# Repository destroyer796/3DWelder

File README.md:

# 3DWelder
This is an overbuilt 3D pen designed to be used for "welding" 3D printed parts together using 1.75mm filament. This project is funded by [Hack Club](https://hackclub.com/) as a part of the [Highway](https://highway.hackclub.com/) program.

Keep in mind for time being PCB is not working, I'll update soon.

This design uses a CHC Pro hotend and a custom Orbiter extruder adapted to use a DC motor. This DC motor's speed is controlled by a drill trigger adapted into the handle. It has a small screen and a rotary encoder for adjusting and showing the temperature target. The whole thing is powered by a drill battery to make it more portable and easier to use. This project is currently completely untested.

## Why?
So, why did I choose to make this ridiculous thing anyways? Well, the best way to join 3D printed parts together if they can't be screwed is by literally joining them together with the same plastic they're made of. This can be very difficult with a normal 3D pen though, as they're quite low powered and actually can't even melt many higher temperature plastics. I wanted a solution to this, so I decided to basically make a regular 3D printer extruding setup, but make it portable. It has some other uses aswell, if you use EVA filament, it could function essentially as a hot glue gun. It could also theoretically be used as a 3D pen, but not that well.

## PCB

The pcb was designed using KiCad, and it is only 2 layers. The pcb controlls everything except for voltage control and the motor, which is controlled by the drill trigger. It uses screw terminals and jst-xh connections. The brains of the whole thing is an Arduino Nano.

## Wiring/Assembly

All 3D printed parts screw together using M3 heatset inserts and various M3/M4 screws. For wiring, 2 spade connectors are used as terminals on the battery. From there, there's 2 ways of wiring everything else. You can either put the buck converter inside the space above the battery, then have wires coming off of that to the drill trigger and pcb, or have the buck converter up by the pcb, then have wires going back down to the drill trigger. Having the Buck converter in the handle is much cleaner, but may be very difficult to fit inside that small space.

## Code
<details>
  <summary>
    Arduino Code
  </summary>
  
  ~~~
  #include <PID_v1.h>
  #include <Adafruit_SSD1306.h>
  #include <Adafruit_GFX.h>
  #include <Wire.h>
  
  //Defines screen width/height
  #define SCREEN_WIDTH 128
  #define SCREEN_HEIGHT 32
  
  //Not using a reset pin
  #define OLED_RESET -1
  
  //Creates a display named display, gives it parameters
  Adafruit_SSD1306 display(SCREEN_WIDTH, SCREEN_HEIGHT, &Wire, OLED_RESET);
  
  // EC11 code
  const int EC11PinA = 8;
  const int EC11PinB = 7;
  volatile in encoderPos = 0;
  in lastEncoded = 0;
  
  /* -----------  USER SETTINGS  ----------- */
  const int   thermistorPin   = A0;
  const int   heaterPin       = 6;     // PWM pin
  const int   statusLedPin    = 13;    // Built‑in LED on most Arduinos
  const float R_FIXED         = 100000.0;   // 100 kΩ divider resistor
  
  // Steinhart–Hart coefficients for Semitec 104GT‑2 / 104NT
  const float A = 1.009249522e-3;
  const float B = 2.378405444e-4;
  const float C = 2.019202697e-7;
  
  // PID tuning
  double Kp = 4.0, Ki = 0.3, Kd = 12.0;
  
  /* Temperature targets */
  double setpointC   = 60.0;   // Desired temperature
  const double MAX_TEMP_C      = 300.0;   // Hard safety limit
  const double MIN_VALID_VOLT  = 0.10;   // Thermistor‑open detection
  
  /* -----------  GLOBALS  ----------- */
  double inputC, outputPWM;          // For PID library
  PID myPID(&inputC, &outputPWM, &setpointC, Kp, Ki, Kd, DIRECT);
  
  enum FaultState { OK, OVER_TEMPERATURE, SENSOR_ERROR };
  FaultState fault = OK;
  
  /* Timing helpers */
  unsigned long lastBlink   = 0;
  bool          ledState    = false;
  
  void setup() {
    //Start I2C
    Wire.begin();
  
    // Initializes display using I2C address 0x3C, if it fails it prints error message
    // Switchcapvcc thing tells it that display has internal voltage regulator
    if (!display.begin(SSD1306_SWITCHCAPVCC, 0x3C)) {
      Serial.begin(9600);
      Serial.println(F("SSD1306 allocation failed"));
      for (;;);
    }
  
    //Display test commands
    display.clearDisplay(); // Clears display
    display.setTextSize(1); // Sets text size, 1 = 6/8 pixels, 5/7 without spacing, 2 = 2x, 3 = 3x
    display.setTextColor(SSD1306_WHITE); // Set white text
    display.setCursor(0,0); // Sets cursor to top-left
    display.println(F("Hello SH-S091!")); // Print message to display buffer
    display.display(); // Push everything in buffer to scren
    // display.setFont(), allows you to change fonts, need to install them
    // display.fillRect(x, y, width, height, SSD1306_BLACK) draws a black rect, way to clear part of screen
  
    //EC11 Code
    pinMode(EC11PinA, INPUT_PULLUP);
    pinMode(EC11PinB, INPUT_PULLUP);
    attachInterrupt(digitalPinToInterrupt(EC11PinA), updateEncoder, CHANGE);
    attachInterrupt(digitalPinToInterrupt(EC11PinB), updateEncoder, CHANGE);

    pinMode(heaterPin,   OUTPUT);
    pinMode(statusLedPin, OUTPUT);
    Serial.begin(9600);
  
    myPID.SetOutputLimits(0, 255);
    myPID.SetSampleTime(250);          // 4 Hz PID updates
    myPID.SetMode(AUTOMATIC);
  }
  
  void loop() {
    //EC11 Code
    static int lastPos = 0;
    if (encoderPos != lastPos) {
      Serial.print("Value: ");
      Serial.println(encoderPos);
  
      display.fillRect(0, 0, 64, 32, SSD1306_BLACK);
      display.setTextSize(1);
      display.setTextColor(SSD1306_WHITE);
      display.setCursor(0,0);
      display.println(F(encoderPos));
      display.display
  
      lastPos = encoderPos;
    }

    /* ---------- Read thermistor ---------- */
    int   adc = analogRead(thermistorPin);
    float v   = adc * 5.0 / 1023.0;
  
    /* Sensor fault check */
    if (v < MIN_VALID_VOLT)  fault = SENSOR_ERROR;
  
    /* Convert to °C if no sensor fault */
    if (fault == OK) {
      double R = R_FIXED * (5.0 / v - 1.0);
      double lnR = log(R);
      double tempK = 1.0 / (A + B*lnR + C*lnR*lnR*lnR);
      inputC = tempK - 273.15;
  
      /* Over‑temperature check */
      if (inputC >= MAX_TEMP_C) fault = OVER_TEMPERATURE;
    }
  
    /* ---------- Safety Handling ---------- */
    if (fault != OK) {
      myPID.SetMode(MANUAL);       // Freeze PID
      outputPWM = 0;               // Heater OFF
      analogWrite(heaterPin, 0);
    } else {
      myPID.Compute();             // Let PID calculate outputPWM
      analogWrite(heaterPin, (int)outputPWM);
    }
  
    /* ---------- Status LED ----------
       • ON  …… actively heating (PWM > 0)
       • Slow blink …… at set‑point (PID output ~0)
       • Fast blink …… fault
    ---------------------------------- */
    unsigned long now = millis();
    unsigned long blinkPeriod =
        (fault != OK)          ? 150 :        // fast blink on fault
        (outputPWM < 2)        ? 800 :        // slow blink at set‑point
                                 0;           // solid ON while heating
  
    if (blinkPeriod == 0) {
      digitalWrite(statusLedPin, HIGH);
    } else if (now - lastBlink >= blinkPeriod) {
      ledState = !ledState;
      digitalWrite(statusLedPin, ledState);
      lastBlink = now;
    }
  
    /* ---------- Serial Monitor ---------- */
    Serial.print("Temp: ");
    Serial.print((fault == OK) ? inputC : NAN);
    Serial.print(" °C | PWM: ");
    Serial.print(outputPWM);
    Serial.print(" | Fault: ");
    Serial.println(
        (fault == OK) ? "None" :
        (fault == OVER_TEMPERATURE) ? "Over-Temp" : "Sensor Error");

    // Shows temp on display
    display.fillRect(64, 0, 64, 32, SSD1306_BLACK);
    display.setTextSize(1);
    display.setTextColor(SSD1306_WHITE);
    display.setCursor(64,0);
    display.println(F(inputC));
    display.display
  }
  
  //EC11 code, runs everytime a change in position is detected
  void updateEncoder() {
    int MSB = digitalREad(EC11PinA);
    int LSB = digitalRead(EC11PinB);
  
    int encoded = (MSB << 1) | LSB;
    int sum = (lastEncocded << 2) | encoded;
  
    //Clockwise
    if (sum == 0b1101 || sum == 0b0100 || sum == 0b0010 || sum == 0b1011) {
      encoderPos += 5;
    }
    //Counter-Clockwise
    if (sum == 0b1110 || sum == 0b0111 || sum == 0b0001 || sum == 0b1000) {
      encoderPos -= 5;
    }
  
    lastEncoded = encoded
  }
  ~~~

</details>

This is the firmware to be uploaded to the Arduino Nano. It's purpose is for PID control of the heater via the thermistor readings and mosfet. It has temperature control via the EC11 rotary encoder, and the temperature target and current temperature are displayed on the 0.91 inch OLED screen.

## BOM

| Item | Quantity | Price | Source | Notes | Owned/Buying |
|--------|--------|--------|--------|--------|--------|
| Drill Trigger | 1 | $3.57 | [Aliexpress](https://www.aliexpress.com/item/3256806562336203.html?spm=a2g0o.cart.0.0.755738danhf7AI&mp=1&pdp_npi=5%40dis%21USD%21USD%209.39%21USD%203.57%21%21USD%203.57%21%21%21%402103146c17528271550647744ef8ea%2112000038176249576%21ct%21US%212965353747%21%211%210&_gl=1*1qs30jx*_gcl_aw*R0NMLjE3NTE4NDcxMzYuQ2owS0NRand2YWpEQmhDTkFSSXNBRUUyOVdvb1JYN0FnSzczYmNCVXN5VHRNRGlUUjV4QXJ0RzRDSVl6Tmx5ZEZ2alByYWdRQjczVklkSWFBc3FnRUFMd193Y0I.*_gcl_dc*R0NMLjE3NTE4NDcxMzYuQ2owS0NRand2YWpEQmhDTkFSSXNBRUUyOVdvb1JYN0FnSzczYmNCVXN5VHRNRGlUUjV4QXJ0RzRDSVl6Tmx5ZEZ2alByYWdRQjczVklkSWFBc3FnRUFMd193Y0I.*_gcl_au*MTM0OTQyNjgzMy4xNzUwMTkyNzY4*_ga*MjcyMzA3OTUzLjE3NTI4MjM0NjE.*_ga_VED1YSGNC7*czE3NTI4MjM0NjEkbzEkZzEkdDE3NTI4MjcwNjAkajU5JGwwJGgw) | For regulating motor | Buying |
| CHC Pro | 1 | $22.42 | [Aliexpress](https://www.aliexpress.com/item/3256806914810913.html?spm=a2g0o.cart.0.0.755738daw2eCeF&mp=1&pdp_npi=5%40dis%21USD%21USD%2049.83%21USD%2022.42%21%21USD%2022.42%21%21%21%402101e07217528229181472693e61f9%2112000045551090949%21ct%21US%212965353747%21%211%210&_gl=1*1s341fi*_gcl_aw*R0NMLjE3NTE4NDcxMzYuQ2owS0NRand2YWpEQmhDTkFSSXNBRUUyOVdvb1JYN0FnSzczYmNCVXN5VHRNRGlUUjV4QXJ0RzRDSVl6Tmx5ZEZ2alByYWdRQjczVklkSWFBc3FnRUFMd193Y0I.*_gcl_dc*R0NMLjE3NTE4NDcxMzYuQ2owS0NRand2YWpEQmhDTkFSSXNBRUUyOVdvb1JYN0FnSzczYmNCVXN5VHRNRGlUUjV4QXJ0RzRDSVl6Tmx5ZEZ2alByYWdRQjczVklkSWFBc3FnRUFMd193Y0I.*_gcl_au*MTM0OTQyNjgzMy4xNzUwMTkyNzY4*_ga*MjcyMzA3OTUzLjE3NTI4MjM0NjE.*_ga_VED1YSGNC7*czE3NTI4MjM0NjEkbzEkZzEkdDE3NTI4MjM1OTkkajIwJGwwJGgw) | Hotend | Buying |
| Screw Terminal 4P | 1 | $2.50 | [Aliexpress](https://www.aliexpress.com/item/3256807282935438.html?spm=a2g0o.cart.0.0.755738danhf7AI&mp=1&pdp_npi=5%40dis%21USD%21USD%202.59%21USD%202.50%21%21USD%202.50%21%21%21%402103146c17528271550647744ef8ea%2112000040883353771%21ct%21US%212965353747%21%211%210&_gl=1*1qs30jx*_gcl_aw*R0NMLjE3NTE4NDcxMzYuQ2owS0NRand2YWpEQmhDTkFSSXNBRUUyOVdvb1JYN0FnSzczYmNCVXN5VHRNRGlUUjV4QXJ0RzRDSVl6Tmx5ZEZ2alByYWdRQjczVklkSWFBc3FnRUFMd193Y0I.*_gcl_dc*R0NMLjE3NTE4NDcxMzYuQ2owS0NRand2YWpEQmhDTkFSSXNBRUUyOVdvb1JYN0FnSzczYmNCVXN5VHRNRGlUUjV4QXJ0RzRDSVl6Tmx5ZEZ2alByYWdRQjczVklkSWFBc3FnRUFMd193Y0I.*_gcl_au*MTM0OTQyNjgzMy4xNzUwMTkyNzY4*_ga*MjcyMzA3OTUzLjE3NTI4MjM0NjE.*_ga_VED1YSGNC7*czE3NTI4MjM0NjEkbzEkZzEkdDE3NTI4MjcwNjAkajU5JGwwJGgw) | 7.62mm pitch, Power inputs | Buying |
| Screw Terminal 2P | 1 | $1.87 | [Aliexpress](https://www.aliexpress.com/item/3256807282935438.html?spm=a2g0o.cart.0.0.755738danhf7AI&mp=1&pdp_npi=5%40dis%21USD%21USD%201.94%21USD%201.87%21%21USD%201.87%21%21%21%402103146c17528271550647744ef8ea%2112000040883353769%21ct%21US%212965353747%21%211%210&_gl=1*1qs30jx*_gcl_aw*R0NMLjE3NTE4NDcxMzYuQ2owS0NRand2YWpEQmhDTkFSSXNBRUUyOVdvb1JYN0FnSzczYmNCVXN5VHRNRGlUUjV4QXJ0RzRDSVl6Tmx5ZEZ2alByYWdRQjczVklkSWFBc3FnRUFMd193Y0I.*_gcl_dc*R0NMLjE3NTE4NDcxMzYuQ2owS0NRand2YWpEQmhDTkFSSXNBRUUyOVdvb1JYN0FnSzczYmNCVXN5VHRNRGlUUjV4QXJ0RzRDSVl6Tmx5ZEZ2alByYWdRQjczVklkSWFBc3FnRUFMd193Y0I.*_gcl_au*MTM0OTQyNjgzMy4xNzUwMTkyNzY4*_ga*MjcyMzA3OTUzLjE3NTI4MjM0NjE.*_ga_VED1YSGNC7*czE3NTI4MjM0NjEkbzEkZzEkdDE3NTI4MjcwNjAkajU5JGwwJGgw) | 7.62mm pitch, Heater outputs | Buying |
| 2510 24V Fan | 1 | $2.08 | [Aliexpress](https://www.aliexpress.com/item/3256807251337149.html?spm=a2g0o.cart.0.0.755738danhf7AI&mp=1&pdp_npi=5%40dis%21USD%21USD%202.18%21USD%202.08%21%21USD%202.08%21%21%21%402103146c17528271550647744ef8ea%2112000040754390185%21ct%21US%212965353747%21%211%210&_gl=1*1qs30jx*_gcl_aw*R0NMLjE3NTE4NDcxMzYuQ2owS0NRand2YWpEQmhDTkFSSXNBRUUyOVdvb1JYN0FnSzczYmNCVXN5VHRNRGlUUjV4QXJ0RzRDSVl6Tmx5ZEZ2alByYWdRQjczVklkSWFBc3FnRUFMd193Y0I.*_gcl_dc*R0NMLjE3NTE4NDcxMzYuQ2owS0NRand2YWpEQmhDTkFSSXNBRUUyOVdvb1JYN0FnSzczYmNCVXN5VHRNRGlUUjV4QXJ0RzRDSVl6Tmx5ZEZ2alByYWdRQjczVklkSWFBc3FnRUFMd193Y0I.*_gcl_au*MTM0OTQyNjgzMy4xNzUwMTkyNzY4*_ga*MjcyMzA3OTUzLjE3NTI4MjM0NjE.*_ga_VED1YSGNC7*czE3NTI4MjM0NjEkbzEkZzEkdDE3NTI4MjcwNjAkajU5JGwwJGgw) | Cools hotend | Owned |
| EC11 Rotary Encoder | 1 | $3.08 | [Aliexpress](https://www.aliexpress.com/item/3256805796819763.html?spm=a2g0o.cart.0.0.755738danhf7AI&mp=1&pdp_npi=5%40dis%21USD%21USD%203.08%21USD%203.08%21%21USD%203.08%21%21%21%402103146c17528271550647744ef8ea%2112000035172713579%21ct%21US%212965353747%21%211%210&_gl=1*1gfgklc*_gcl_aw*R0NMLjE3NTE4NDcxMzYuQ2owS0NRand2YWpEQmhDTkFSSXNBRUUyOVdvb1JYN0FnSzczYmNCVXN5VHRNRGlUUjV4QXJ0RzRDSVl6Tmx5ZEZ2alByYWdRQjczVklkSWFBc3FnRUFMd193Y0I.*_gcl_dc*R0NMLjE3NTE4NDcxMzYuQ2owS0NRand2YWpEQmhDTkFSSXNBRUUyOVdvb1JYN0FnSzczYmNCVXN5VHRNRGlUUjV4QXJ0RzRDSVl6Tmx5ZEZ2alByYWdRQjczVklkSWFBc3FnRUFMd193Y0I.*_gcl_au*MTM0OTQyNjgzMy4xNzUwMTkyNzY4*_ga*MjcyMzA3OTUzLjE3NTI4MjM0NjE.*_ga_VED1YSGNC7*czE3NTI4MjM0NjEkbzEkZzEkdDE3NTI4MjcwNjAkajU5JGwwJGgw) | For controlling temp | Buying |
| I2C OLED | 1 | $1.85 | [Aliexpress](https://www.aliexpress.com/item/3256806179530924.html?spm=a2g0o.cart.0.0.755738danhf7AI&mp=1&pdp_npi=5%40dis%21USD%21USD%204.03%21USD%201.85%21%21USD%201.85%21%21%21%402103146c17528271550647744ef8ea%2112000036911966887%21ct%21US%212965353747%21%211%210&_gl=1*1gfgklc*_gcl_aw*R0NMLjE3NTE4NDcxMzYuQ2owS0NRand2YWpEQmhDTkFSSXNBRUUyOVdvb1JYN0FnSzczYmNCVXN5VHRNRGlUUjV4QXJ0RzRDSVl6Tmx5ZEZ2alByYWdRQjczVklkSWFBc3FnRUFMd193Y0I.*_gcl_dc*R0NMLjE3NTE4NDcxMzYuQ2owS0NRand2YWpEQmhDTkFSSXNBRUUyOVdvb1JYN0FnSzczYmNCVXN5VHRNRGlUUjV4QXJ0RzRDSVl6Tmx5ZEZ2alByYWdRQjczVklkSWFBc3FnRUFMd193Y0I.*_gcl_au*MTM0OTQyNjgzMy4xNzUwMTkyNzY4*_ga*MjcyMzA3OTUzLjE3NTI4MjM0NjE.*_ga_VED1YSGNC7*czE3NTI4MjM0NjEkbzEkZzEkdDE3NTI4MjcwNjAkajU5JGwwJGgw) | 0.91in, Displays target/current temp | Buying |
| TO-220 Radiator | 1 | $1.94 | [Aliexpress](https://www.aliexpress.com/item/2255800003999447.html?spm=a2g0o.cart.0.0.755738danhf7AI&mp=1&pdp_npi=5%40dis%21USD%21USD%202.01%21USD%201.94%21%21USD%201.94%21%21%21%402103146c17528271550647744ef8ea%2110000000710306628%21ct%21US%212965353747%21%211%210&_gl=1*1gfgklc*_gcl_aw*R0NMLjE3NTE4NDcxMzYuQ2owS0NRand2YWpEQmhDTkFSSXNBRUUyOVdvb1JYN0FnSzczYmNCVXN5VHRNRGlUUjV4QXJ0RzRDSVl6Tmx5ZEZ2alByYWdRQjczVklkSWFBc3FnRUFMd193Y0I.*_gcl_dc*R0NMLjE3NTE4NDcxMzYuQ2owS0NRand2YWpEQmhDTkFSSXNBRUUyOVdvb1JYN0FnSzczYmNCVXN5VHRNRGlUUjV4QXJ0RzRDSVl6Tmx5ZEZ2alByYWdRQjczVklkSWFBc3FnRUFMd193Y0I.*_gcl_au*MTM0OTQyNjgzMy4xNzUwMTkyNzY4*_ga*MjcyMzA3OTUzLjE3NTI4MjM0NjE.*_ga_VED1YSGNC7*czE3NTI4MjM0NjEkbzEkZzEkdDE3NTI4MjcwNjAkajU5JGwwJGgw) | Cools mosfet | Buying |
| IRLZ34NPBF Mosfet | 1 | $3.20 | [Aliexpress](https://www.aliexpress.com/item/3256808552158121.html?spm=a2g0o.cart.0.0.755738danhf7AI&mp=1&pdp_npi=5%40dis%21USD%21USD%206.97%21USD%203.20%21%21USD%203.20%21%21%21%402103146c17528271550647744ef8ea%2112000046468959878%21ct%21US%212965353747%21%211%210&_gl=1*1gfgklc*_gcl_aw*R0NMLjE3NTE4NDcxMzYuQ2owS0NRand2YWpEQmhDTkFSSXNBRUUyOVdvb1JYN0FnSzczYmNCVXN5VHRNRGlUUjV4QXJ0RzRDSVl6Tmx5ZEZ2alByYWdRQjczVklkSWFBc3FnRUFMd193Y0I.*_gcl_dc*R0NMLjE3NTE4NDcxMzYuQ2owS0NRand2YWpEQmhDTkFSSXNBRUUyOVdvb1JYN0FnSzczYmNCVXN5VHRNRGlUUjV4QXJ0RzRDSVl6Tmx5ZEZ2alByYWdRQjczVklkSWFBc3FnRUFMd193Y0I.*_gcl_au*MTM0OTQyNjgzMy4xNzUwMTkyNzY4*_ga*MjcyMzA3OTUzLjE3NTI4MjM0NjE.*_ga_VED1YSGNC7*czE3NTI4MjM0NjEkbzEkZzEkdDE3NTI4MjcwNjAkajU5JGwwJGgw) | TO-220, Regulates hotend heater | Buying |
| 24V-12V Buck Converter | 1 | $4.12 | [Aliexpress](https://www.aliexpress.com/item/3256805319593185.html?spm=a2g0o.cart.0.0.755738danhf7AI&mp=1&pdp_npi=5%40dis%21USD%21USD%204.12%21USD%204.12%21%21USD%204.12%21%21%21%402103146c17528271550647744ef8ea%2112000033343621926%21ct%21US%212965353747%21%211%210&_gl=1*1gfgklc*_gcl_aw*R0NMLjE3NTE4NDcxMzYuQ2owS0NRand2YWpEQmhDTkFSSXNBRUUyOVdvb1JYN0FnSzczYmNCVXN5VHRNRGlUUjV4QXJ0RzRDSVl6Tmx5ZEZ2alByYWdRQjczVklkSWFBc3FnRUFMd193Y0I.*_gcl_dc*R0NMLjE3NTE4NDcxMzYuQ2owS0NRand2YWpEQmhDTkFSSXNBRUUyOVdvb1JYN0FnSzczYmNCVXN5VHRNRGlUUjV4QXJ0RzRDSVl6Tmx5ZEZ2alByYWdRQjczVklkSWFBc3FnRUFMd193Y0I.*_gcl_au*MTM0OTQyNjgzMy4xNzUwMTkyNzY4*_ga*MjcyMzA3OTUzLjE3NTI4MjM0NjE.*_ga_VED1YSGNC7*czE3NTI4MjM0NjEkbzEkZzEkdDE3NTI4MjcwNjAkajU5JGwwJGgw) | Converts battery 24V to 12V for Arduino | Buying |
| DC Motor | 1 | $13.35 | [Aliexpress](https://www.aliexpress.com/item/3256807142640791.html?spm=a2g0o.cart.0.0.755738danhf7AI&mp=1&pdp_npi=5%40dis%21USD%21USD%2029.02%21USD%2013.35%21%21USD%2013.35%21%21%21%402103146c17528271595267798ef8ea%2112000040287640067%21ct%21US%212965353747%21%211%210&_gl=1*1djn14*_gcl_aw*R0NMLjE3NTE4NDcxMzYuQ2owS0NRand2YWpEQmhDTkFSSXNBRUUyOVdvb1JYN0FnSzczYmNCVXN5VHRNRGlUUjV4QXJ0RzRDSVl6Tmx5ZEZ2alByYWdRQjczVklkSWFBc3FnRUFMd193Y0I.*_gcl_dc*R0NMLjE3NTE4NDcxMzYuQ2owS0NRand2YWpEQmhDTkFSSXNBRUUyOVdvb1JYN0FnSzczYmNCVXN5VHRNRGlUUjV4QXJ0RzRDSVl6Tmx5ZEZ2alByYWdRQjczVklkSWFBc3FnRUFMd193Y0I.*_gcl_au*MTM0OTQyNjgzMy4xNzUwMTkyNzY4*_ga*MjcyMzA3OTUzLjE3NTI4MjM0NjE.*_ga_VED1YSGNC7*czE3NTI4MjM0NjEkbzEkZzEkdDE3NTI4MjcwNjAkajU5JGwwJGgw) | 24V, Worm gear, 27rpm, drives extruder | Buying |
| Kobalt 24V Battery | 1 | $28.35 | [Aliexpress](https://www.aliexpress.com/item/3256808341351094.html?spm=a2g0o.cart.0.0.755738danhf7AI&mp=1&pdp_npi=5%40dis%21USD%21USD%2098.74%21USD%2028.35%21%21USD%2028.35%21%21%21%402103146c17528271595267798ef8ea%2112000045570945299%21ct%21US%212965353747%21%211%210&_gl=1*1djn14*_gcl_aw*R0NMLjE3NTE4NDcxMzYuQ2owS0NRand2YWpEQmhDTkFSSXNBRUUyOVdvb1JYN0FnSzczYmNCVXN5VHRNRGlUUjV4QXJ0RzRDSVl6Tmx5ZEZ2alByYWdRQjczVklkSWFBc3FnRUFMd193Y0I.*_gcl_dc*R0NMLjE3NTE4NDcxMzYuQ2owS0NRand2YWpEQmhDTkFSSXNBRUUyOVdvb1JYN0FnSzczYmNCVXN5VHRNRGlUUjV4QXJ0RzRDSVl6Tmx5ZEZ2alByYWdRQjczVklkSWFBc3FnRUFMd193Y0I.*_gcl_au*MTM0OTQyNjgzMy4xNzUwMTkyNzY4*_ga*MjcyMzA3OTUzLjE3NTI4MjM0NjE.*_ga_VED1YSGNC7*czE3NTI4MjM0NjEkbzEkZzEkdDE3NTI4MjcwNjAkajU5JGwwJGgw) | Any Ah, mines 6.0Ah, Powers whole thing | Buying |
| 100k Resistor | 1 | $1.27 | [Aliexpress](https://www.aliexpress.us/item/3256805491339263.html?spm=a2g0o.productlist.main.2.5acb113dWCWHEi&algo_pvid=d885d319-e63c-46cb-9890-1f3fe4b1ec6b&algo_exp_id=d885d319-e63c-46cb-9890-1f3fe4b1ec6b-1&pdp_ext_f=%7B%22order%22%3A%221339%22%2C%22eval%22%3A%221%22%7D&pdp_npi=4%40dis%21USD%211.88%211.26%21%21%2113.46%219.02%21%402103247917528275691891949e5c61%2112000033982954181%21sea%21US%212965353747%21X&curPageLogUid=0ChrWbtCVhkG&utparam-url=scene%3Asearch%7Cquery_from%3A) | For thermistor logic | Owned |
| 10k Resistor | 1 | $1.34 | [Aliexpress](https://www.aliexpress.us/item/3256805491339263.html?spm=a2g0o.productlist.main.2.5acb113dWCWHEi&algo_pvid=d885d319-e63c-46cb-9890-1f3fe4b1ec6b&algo_exp_id=d885d319-e63c-46cb-9890-1f3fe4b1ec6b-1&pdp_ext_f=%7B%22order%22%3A%221339%22%2C%22eval%22%3A%221%22%7D&pdp_npi=4%40dis%21USD%211.88%211.26%21%21%2113.46%219.02%21%402103247917528275691891949e5c61%2112000033982954181%21sea%21US%212965353747%21X&curPageLogUid=0ChrWbtCVhkG&utparam-url=scene%3Asearch%7Cquery_from%3A) | Heater gate pulldown | Owned |
| 220R Resistor | 1 | $1.35 | [Aliexpress](https://www.aliexpress.us/item/3256805491339263.html?spm=a2g0o.productlist.main.2.5acb113dWCWHEi&algo_pvid=d885d319-e63c-46cb-9890-1f3fe4b1ec6b&algo_exp_id=d885d319-e63c-46cb-9890-1f3fe4b1ec6b-1&pdp_ext_f=%7B%22order%22%3A%221339%22%2C%22eval%22%3A%221%22%7D&pdp_npi=4%40dis%21USD%211.88%211.26%21%21%2113.46%219.02%21%402103247917528275691891949e5c61%2112000033982954181%21sea%21US%212965353747%21X&curPageLogUid=0ChrWbtCVhkG&utparam-url=scene%3Asearch%7Cquery_from%3A) | Heater gate drive | Owned |
| 2 Pin JST XH Female | 2 | $2.37 | [Aliexpress](https://www.aliexpress.com/item/3256803235887618.html?spm=a2g0o.cart.0.0.755738danhf7AI&mp=1&pdp_npi=5%40dis%21USD%21USD%202.49%21USD%202.37%21%21USD%202.37%21%21%21%402103146c17528270600956401ef8ea%2112000025716082487%21ct%21US%212965353747%21%211%210&_gl=1*1djn14*_gcl_aw*R0NMLjE3NTE4NDcxMzYuQ2owS0NRand2YWpEQmhDTkFSSXNBRUUyOVdvb1JYN0FnSzczYmNCVXN5VHRNRGlUUjV4QXJ0RzRDSVl6Tmx5ZEZ2alByYWdRQjczVklkSWFBc3FnRUFMd193Y0I.*_gcl_dc*R0NMLjE3NTE4NDcxMzYuQ2owS0NRand2YWpEQmhDTkFSSXNBRUUyOVdvb1JYN0FnSzczYmNCVXN5VHRNRGlUUjV4QXJ0RzRDSVl6Tmx5ZEZ2alByYWdRQjczVklkSWFBc3FnRUFMd193Y0I.*_gcl_au*MTM0OTQyNjgzMy4xNzUwMTkyNzY4*_ga*MjcyMzA3OTUzLjE3NTI4MjM0NjE.*_ga_VED1YSGNC7*czE3NTI4MjM0NjEkbzEkZzEkdDE3NTI4MjcwNjAkajU5JGwwJGgw) | For fan and thermistor | Owned |
| 18 AWG Wire | ~2 meters | $2.11 | [Aliexpress](https://www.aliexpress.com/item/3256806379805687.html?spm=a2g0o.cart.0.0.755738danhf7AI&mp=1&pdp_npi=5%40dis%21USD%21USD%202.20%21USD%202.11%21%21USD%202.11%21%21%21%402103146c17528270600956401ef8ea%2112000037691464120%21ct%21US%212965353747%21%211%210&_gl=1*1djn14*_gcl_aw*R0NMLjE3NTE4NDcxMzYuQ2owS0NRand2YWpEQmhDTkFSSXNBRUUyOVdvb1JYN0FnSzczYmNCVXN5VHRNRGlUUjV4QXJ0RzRDSVl6Tmx5ZEZ2alByYWdRQjczVklkSWFBc3FnRUFMd193Y0I.*_gcl_dc*R0NMLjE3NTE4NDcxMzYuQ2owS0NRand2YWpEQmhDTkFSSXNBRUUyOVdvb1JYN0FnSzczYmNCVXN5VHRNRGlUUjV4QXJ0RzRDSVl6Tmx5ZEZ2alByYWdRQjczVklkSWFBc3FnRUFMd193Y0I.*_gcl_au*MTM0OTQyNjgzMy4xNzUwMTkyNzY4*_ga*MjcyMzA3OTUzLjE3NTI4MjM0NjE.*_ga_VED1YSGNC7*czE3NTI4MjM0NjEkbzEkZzEkdDE3NTI4MjcwNjAkajU5JGwwJGgw) | Wiring everything | Owned |
| Arduino Nano | 1 | $2.94 | [Aliexpress](https://www.aliexpress.com/item/3256806587205161.html?spm=a2g0o.cart.0.0.755738danhf7AI&mp=1&pdp_npi=5%40dis%21USD%21USD%202.94%21USD%202.94%21%21USD%202.94%21%21%21%402103146c17528270600956401ef8ea%2112000038256018925%21ct%21US%212965353747%21%211%210&_gl=1*6iw3e9*_gcl_aw*R0NMLjE3NTE4NDcxMzYuQ2owS0NRand2YWpEQmhDTkFSSXNBRUUyOVdvb1JYN0FnSzczYmNCVXN5VHRNRGlUUjV4QXJ0RzRDSVl6Tmx5ZEZ2alByYWdRQjczVklkSWFBc3FnRUFMd193Y0I.*_gcl_dc*R0NMLjE3NTE4NDcxMzYuQ2owS0NRand2YWpEQmhDTkFSSXNBRUUyOVdvb1JYN0FnSzczYmNCVXN5VHRNRGlUUjV4QXJ0RzRDSVl6Tmx5ZEZ2alByYWdRQjczVklkSWFBc3FnRUFMd193Y0I.*_gcl_au*MTM0OTQyNjgzMy4xNzUwMTkyNzY4*_ga*MjcyMzA3OTUzLjE3NTI4MjM0NjE.*_ga_VED1YSGNC7*czE3NTI4MjM0NjEkbzEkZzEkdDE3NTI4MjcwNjAkajU5JGwwJGgw) | Type C, Microprocessor | Buying |
| M3 Heatset Inserts | ~18 | $2.05 | [Aliexpress](https://www.aliexpress.com/item/3256803396040989.html?spm=a2g0o.cart.0.0.755738danhf7AI&mp=1&pdp_npi=5%40dis%21USD%21USD%202.17%21USD%202.05%21%21USD%202.05%21%21%21%402103146c17528270600956401ef8ea%2112000026370649758%21ct%21US%212965353747%21%211%210&_gl=1*6iw3e9*_gcl_aw*R0NMLjE3NTE4NDcxMzYuQ2owS0NRand2YWpEQmhDTkFSSXNBRUUyOVdvb1JYN0FnSzczYmNCVXN5VHRNRGlUUjV4QXJ0RzRDSVl6Tmx5ZEZ2alByYWdRQjczVklkSWFBc3FnRUFMd193Y0I.*_gcl_dc*R0NMLjE3NTE4NDcxMzYuQ2owS0NRand2YWpEQmhDTkFSSXNBRUUyOVdvb1JYN0FnSzczYmNCVXN5VHRNRGlUUjV4QXJ0RzRDSVl6Tmx5ZEZ2alByYWdRQjczVklkSWFBc3FnRUFMd193Y0I.*_gcl_au*MTM0OTQyNjgzMy4xNzUwMTkyNzY4*_ga*MjcyMzA3OTUzLjE3NTI4MjM0NjE.*_ga_VED1YSGNC7*czE3NTI4MjM0NjEkbzEkZzEkdDE3NTI4MjcwNjAkajU5JGwwJGgw) | M3x5x4, Gives 3D printed parts threads | Owned |
| M3x6 Screws | ~11 | $2.04 | [Aliexpress](https://www.aliexpress.com/item/3256806983352954.html?spm=a2g0o.cart.0.0.755738danhf7AI&mp=1&pdp_npi=5%40dis%21USD%21USD%204.09%21USD%202.04%21%21USD%202.04%21%21%21%402103146c17528270600956401ef8ea%2112000039685363236%21ct%21US%212965353747%21%211%210&_gl=1*6iw3e9*_gcl_aw*R0NMLjE3NTE4NDcxMzYuQ2owS0NRand2YWpEQmhDTkFSSXNBRUUyOVdvb1JYN0FnSzczYmNCVXN5VHRNRGlUUjV4QXJ0RzRDSVl6Tmx5ZEZ2alByYWdRQjczVklkSWFBc3FnRUFMd193Y0I.*_gcl_dc*R0NMLjE3NTE4NDcxMzYuQ2owS0NRand2YWpEQmhDTkFSSXNBRUUyOVdvb1JYN0FnSzczYmNCVXN5VHRNRGlUUjV4QXJ0RzRDSVl6Tmx5ZEZ2alByYWdRQjczVklkSWFBc3FnRUFMd193Y0I.*_gcl_au*MTM0OTQyNjgzMy4xNzUwMTkyNzY4*_ga*MjcyMzA3OTUzLjE3NTI4MjM0NjE.*_ga_VED1YSGNC7*czE3NTI4MjM0NjEkbzEkZzEkdDE3NTI4MjcwNjAkajU5JGwwJGgw) | For mounting pcb, battery terminal, and handle | Owned |
| M3x8 Screws | ~2 | $2.14 | [Aliexpress](https://www.aliexpress.com/item/3256806983352954.html?spm=a2g0o.cart.0.0.755738danhf7AI&mp=1&pdp_npi=5%40dis%21USD%21USD%204.24%21USD%202.12%21%21USD%202.12%21%21%21%402103146c17528270600956401ef8ea%2112000039685363239%21ct%21US%212965353747%21%211%210&_gl=1*6iw3e9*_gcl_aw*R0NMLjE3NTE4NDcxMzYuQ2owS0NRand2YWpEQmhDTkFSSXNBRUUyOVdvb1JYN0FnSzczYmNCVXN5VHRNRGlUUjV4QXJ0RzRDSVl6Tmx5ZEZ2alByYWdRQjczVklkSWFBc3FnRUFMd193Y0I.*_gcl_dc*R0NMLjE3NTE4NDcxMzYuQ2owS0NRand2YWpEQmhDTkFSSXNBRUUyOVdvb1JYN0FnSzczYmNCVXN5VHRNRGlUUjV4QXJ0RzRDSVl6Tmx5ZEZ2alByYWdRQjczVklkSWFBc3FnRUFMd193Y0I.*_gcl_au*MTM0OTQyNjgzMy4xNzUwMTkyNzY4*_ga*MjcyMzA3OTUzLjE3NTI4MjM0NjE.*_ga_VED1YSGNC7*czE3NTI4MjM0NjEkbzEkZzEkdDE3NTI4MjcwNjAkajU5JGwwJGgw) | For Orbiter mount | Owned |
| M3x10 Screws | ~4 | $1.38 | [Aliexpress](https://www.aliexpress.com/item/3256805692722422.html?spm=a2g0o.cart.0.0.755738danhf7AI&mp=1&pdp_npi=5%40dis%21USD%21USD%201.42%21USD%201.38%21%21USD%201.38%21%21%21%402103146c17528270600956401ef8ea%2112000034679037237%21ct%21US%212965353747%21%211%210&_gl=1*6iw3e9*_gcl_aw*R0NMLjE3NTE4NDcxMzYuQ2owS0NRand2YWpEQmhDTkFSSXNBRUUyOVdvb1JYN0FnSzczYmNCVXN5VHRNRGlUUjV4QXJ0RzRDSVl6Tmx5ZEZ2alByYWdRQjczVklkSWFBc3FnRUFMd193Y0I.*_gcl_dc*R0NMLjE3NTE4NDcxMzYuQ2owS0NRand2YWpEQmhDTkFSSXNBRUUyOVdvb1JYN0FnSzczYmNCVXN5VHRNRGlUUjV4QXJ0RzRDSVl6Tmx5ZEZ2alByYWdRQjczVklkSWFBc3FnRUFMd193Y0I.*_gcl_au*MTM0OTQyNjgzMy4xNzUwMTkyNzY4*_ga*MjcyMzA3OTUzLjE3NTI4MjM0NjE.*_ga_VED1YSGNC7*czE3NTI4MjM0NjEkbzEkZzEkdDE3NTI4MjcwNjAkajU5JGwwJGgw) | For mounting Hotend mount and hotend clamp | Owned |
| M4x8 Screws | 8 | $2.03 | [Aliexpress](https://www.aliexpress.com/item/3256806983352954.html?spm=a2g0o.cart.0.0.755738danhf7AI&mp=1&pdp_npi=5%40dis%21USD%21USD%204.05%21USD%202.03%21%21USD%202.03%21%21%21%402103146c17528270600956401ef8ea%2112000049313623910%21ct%21US%212965353747%21%211%210&_gl=1*1cp6qeh*_gcl_aw*R0NMLjE3NTE4NDcxMzYuQ2owS0NRand2YWpEQmhDTkFSSXNBRUUyOVdvb1JYN0FnSzczYmNCVXN5VHRNRGlUUjV4QXJ0RzRDSVl6Tmx5ZEZ2alByYWdRQjczVklkSWFBc3FnRUFMd193Y0I.*_gcl_dc*R0NMLjE3NTE4NDcxMzYuQ2owS0NRand2YWpEQmhDTkFSSXNBRUUyOVdvb1JYN0FnSzczYmNCVXN5VHRNRGlUUjV4QXJ0RzRDSVl6Tmx5ZEZ2alByYWdRQjczVklkSWFBc3FnRUFMd193Y0I.*_gcl_au*MTM0OTQyNjgzMy4xNzUwMTkyNzY4*_ga*MjcyMzA3OTUzLjE3NTI4MjM0NjE.*_ga_VED1YSGNC7*czE3NTI4MjM0NjEkbzEkZzEkdDE3NTI4MjcwNjAkajU5JGwwJGgw) | For motor mounting | Owned |
| Orbiter Gears | 1 | $23.32 | [Aliexpress](https://www.aliexpress.com/item/3256802185372532.html?spm=a2g0o.cart.0.0.755738daqLWaOW&mp=1&pdp_npi=5%40dis%21USD%21USD%2023.32%21USD%2023.32%21%21USD%2023.32%21%21%21%402103146c17528269270114546ef8ea%2112000020383149424%21ct%21US%212965353747%21%211%210&_gl=1*zzjcrw*_gcl_aw*R0NMLjE3NTE4NDcxMzYuQ2owS0NRand2YWpEQmhDTkFSSXNBRUUyOVdvb1JYN0FnSzczYmNCVXN5VHRNRGlUUjV4QXJ0RzRDSVl6Tmx5ZEZ2alByYWdRQjczVklkSWFBc3FnRUFMd193Y0I.*_gcl_dc*R0NMLjE3NTE4NDcxMzYuQ2owS0NRand2YWpEQmhDTkFSSXNBRUUyOVdvb1JYN0FnSzczYmNCVXN5VHRNRGlUUjV4QXJ0RzRDSVl6Tmx5ZEZ2alByYWdRQjczVklkSWFBc3FnRUFMd193Y0I.*_gcl_au*MTM0OTQyNjgzMy4xNzUwMTkyNzY4*_ga*MjcyMzA3OTUzLjE3NTI4MjM0NjE.*_ga_VED1YSGNC7*czE3NTI4MjM0NjEkbzEkZzEkdDE3NTI4MjY4NTgkajU3JGwwJGgw) | Extruder drive gears | Buying |
| Orbiter Handle Shell | 1 | $3.17 | [Aliexpress](https://www.aliexpress.com/item/3256802185372532.html?spm=a2g0o.cart.0.0.755738daqLWaOW&mp=1&pdp_npi=5%40dis%21USD%21USD%203.17%21USD%203.17%21%21USD%203.17%21%21%21%402103146c17528269270114546ef8ea%2112000020383149423%21ct%21US%212965353747%21%211%210&_gl=1*zzjcrw*_gcl_aw*R0NMLjE3NTE4NDcxMzYuQ2owS0NRand2YWpEQmhDTkFSSXNBRUUyOVdvb1JYN0FnSzczYmNCVXN5VHRNRGlUUjV4QXJ0RzRDSVl6Tmx5ZEZ2alByYWdRQjczVklkSWFBc3FnRUFMd193Y0I.*_gcl_dc*R0NMLjE3NTE4NDcxMzYuQ2owS0NRand2YWpEQmhDTkFSSXNBRUUyOVdvb1JYN0FnSzczYmNCVXN5VHRNRGlUUjV4QXJ0RzRDSVl6Tmx5ZEZ2alByYWdRQjczVklkSWFBc3FnRUFMd193Y0I.*_gcl_au*MTM0OTQyNjgzMy4xNzUwMTkyNzY4*_ga*MjcyMzA3OTUzLjE3NTI4MjM0NjE.*_ga_VED1YSGNC7*czE3NTI4MjM0NjEkbzEkZzEkdDE3NTI4MjY4NTgkajU3JGwwJGgw) | Extruder lever + shaft | Buying |
| Orbiter Handle Screw | 1 | $2.67 | [Aliexpress](https://www.aliexpress.com/item/3256802185372532.html?spm=a2g0o.cart.0.0.755738daqLWaOW&mp=1&pdp_npi=5%40dis%21USD%21USD%202.67%21USD%202.67%21%21USD%202.67%21%21%21%402103146c17528269270114546ef8ea%2112000020383149428%21ct%21US%212965353747%21%211%210&_gl=1*zzjcrw*_gcl_aw*R0NMLjE3NTE4NDcxMzYuQ2owS0NRand2YWpEQmhDTkFSSXNBRUUyOVdvb1JYN0FnSzczYmNCVXN5VHRNRGlUUjV4QXJ0RzRDSVl6Tmx5ZEZ2alByYWdRQjczVklkSWFBc3FnRUFMd193Y0I.*_gcl_dc*R0NMLjE3NTE4NDcxMzYuQ2owS0NRand2YWpEQmhDTkFSSXNBRUUyOVdvb1JYN0FnSzczYmNCVXN5VHRNRGlUUjV4QXJ0RzRDSVl6Tmx5ZEZ2alByYWdRQjczVklkSWFBc3FnRUFMd193Y0I.*_gcl_au*MTM0OTQyNjgzMy4xNzUwMTkyNzY4*_ga*MjcyMzA3OTUzLjE3NTI4MjM0NjE.*_ga_VED1YSGNC7*czE3NTI4MjM0NjEkbzEkZzEkdDE3NTI4MjY4NTgkajU3JGwwJGgw) | Extruder lever screw/spring | Buying |
| Alternative Full Orbiter | 1 | $30.30 | [Aliexpress](https://www.aliexpress.us/item/3256803143364574.html?spm=a2g0o.productlist.main.3.32711918kejPC1&algo_pvid=031a119a-d9e4-4ec0-9dbd-65a221c951d0&algo_exp_id=031a119a-d9e4-4ec0-9dbd-65a221c951d0-2&pdp_ext_f=%7B%22order%22%3A%2233%22%2C%22eval%22%3A%221%22%7D&pdp_npi=4%40dis%21USD%2136.80%2130.30%21%21%2136.80%2130.30%21%40210337c117528255697113962ecb0f%2112000028794303599%21sea%21US%212965353747%21X&curPageLogUid=faCfA8m1JzG1&utparam-url=scene%3Asearch%7Cquery_from%3A) | Around same price as above but full kit, worse parts | NOT Buying |
| PTFE Tube | 1 | $1.83 | [Aliexpress](https://www.aliexpress.com/item/3256808595111724.html?spm=a2g0o.cart.0.0.755738daqLWaOW&mp=1&pdp_npi=5%40dis%21USD%21USD%201.90%21USD%201.83%21%21USD%201.83%21%21%21%402103146c17528268578343657ef8ea%2112000046644154648%21ct%21US%212965353747%21%211%210&_gl=1*14pyl8l*_gcl_aw*R0NMLjE3NTE4NDcxMzYuQ2owS0NRand2YWpEQmhDTkFSSXNBRUUyOVdvb1JYN0FnSzczYmNCVXN5VHRNRGlUUjV4QXJ0RzRDSVl6Tmx5ZEZ2alByYWdRQjczVklkSWFBc3FnRUFMd193Y0I.*_gcl_dc*R0NMLjE3NTE4NDcxMzYuQ2owS0NRand2YWpEQmhDTkFSSXNBRUUyOVdvb1JYN0FnSzczYmNCVXN5VHRNRGlUUjV4QXJ0RzRDSVl6Tmx5ZEZ2alByYWdRQjczVklkSWFBc3FnRUFMd193Y0I.*_gcl_au*MTM0OTQyNjgzMy4xNzUwMTkyNzY4*_ga*MjcyMzA3OTUzLjE3NTI4MjM0NjE.*_ga_VED1YSGNC7*czE3NTI4MjM0NjEkbzEkZzEkdDE3NTI4MjY4NTgkajU3JGwwJGgw) | Between extruder and hotend, need very little | Owned |
| Spade Terminals | 2 | $2.38 | [Aliexpress](https://www.aliexpress.com/item/3256802579044914.html?spm=a2g0o.cart.0.0.755738daqLWaOW&mp=1&pdp_npi=5%40dis%21USD%21USD%202.48%21USD%202.38%21%21USD%202.38%21%21%21%402103146c17528268578343657ef8ea%2112000022078614610%21ct%21US%212965353747%21%211%210&_gl=1*14pyl8l*_gcl_aw*R0NMLjE3NTE4NDcxMzYuQ2owS0NRand2YWpEQmhDTkFSSXNBRUUyOVdvb1JYN0FnSzczYmNCVXN5VHRNRGlUUjV4QXJ0RzRDSVl6Tmx5ZEZ2alByYWdRQjczVklkSWFBc3FnRUFMd193Y0I.*_gcl_dc*R0NMLjE3NTE4NDcxMzYuQ2owS0NRand2YWpEQmhDTkFSSXNBRUUyOVdvb1JYN0FnSzczYmNCVXN5VHRNRGlUUjV4QXJ0RzRDSVl6Tmx5ZEZ2alByYWdRQjczVklkSWFBc3FnRUFMd193Y0I.*_gcl_au*MTM0OTQyNjgzMy4xNzUwMTkyNzY4*_ga*MjcyMzA3OTUzLjE3NTI4MjM0NjE.*_ga_VED1YSGNC7*czE3NTI4MjM0NjEkbzEkZzEkdDE3NTI4MjY4NTgkajU3JGwwJGgw) | For battery connection | Owned |
| Custom PCB | 1 | $8.52 | [JLC PCB](https://jlcpcb.com/?from=VGSU&utm_source=google&utm_medium=cpc&utm_campaign=14179457750&gad_source=1&gad_campaignid=14179457750&gbraid=0AAAAABS1QqnKxzJxFraqirNeN0Jsk7SAi&gclid=CjwKCAjw4efDBhATEiwAaDBpbgJS_HEbmtEoijaZsA4da2X2VfovqTt3S1jdUBIx32Qqjq6h8wbXnBoC3nMQAvD_BwE) | For connecting all components |

Total(No shipping/taxes): $148.12   <br>
My Total: $157.54 (with shipping/taxes, excluding owned items)

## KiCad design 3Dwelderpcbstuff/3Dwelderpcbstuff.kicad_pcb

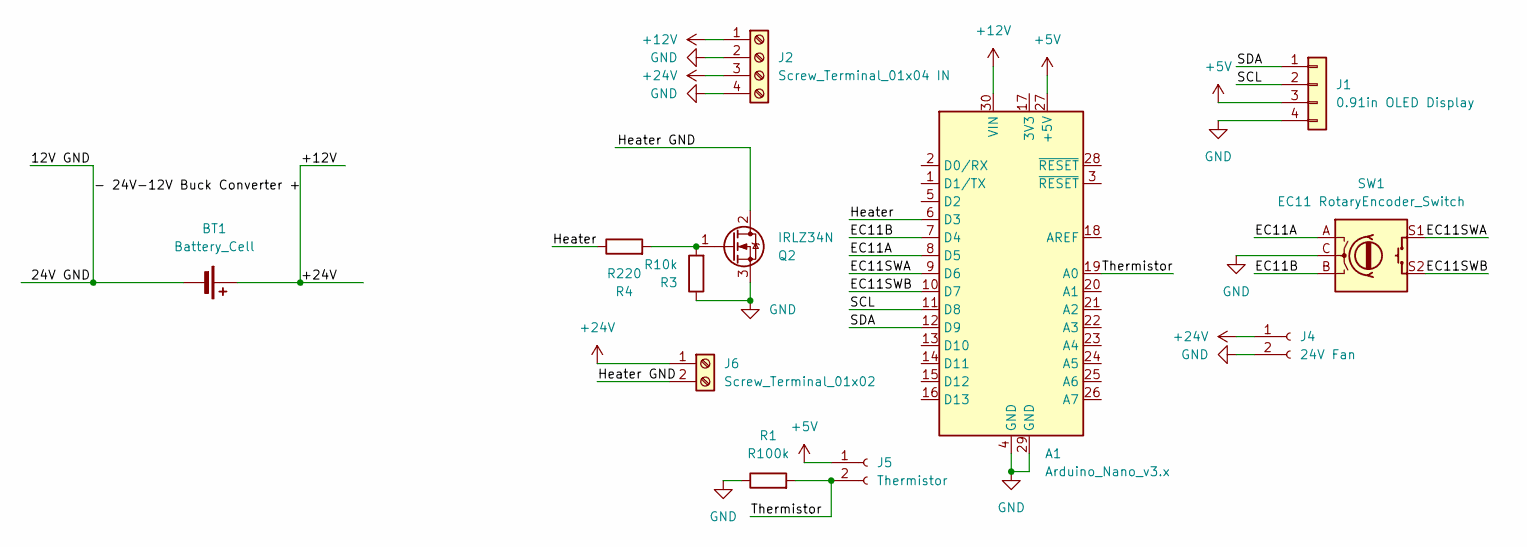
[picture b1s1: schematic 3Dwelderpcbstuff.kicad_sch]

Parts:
A1: Arduino_Nano_v3.x; Arduino_Nano
BT1: Battery_Cell
J1: 0.91in OLED Display; SSD1306-0.91-OLED-4pin-128x32
J2: Screw_Terminal_01x04 IN; Screw Terminal 4 Pin 7.62mmP
J4: 24V Fan; JST_XH_B2B-XH-AM_1x02_P2.50mm_Vertical
J5: Thermistor; JST_XH_B2B-XH-AM_1x02_P2.50mm_Vertical
J6: Screw_Terminal_01x02; Screw Terminal 2 Pin 7.62mmP
Q2: IRLZ34N; TO-220-3_Vertical
R1: R100k; R_0201_0603Metric
R3: R10k; R_0201_0603Metric
R4: R220; R_0201_0603Metric
SW1: EC11 RotaryEncoder_Switch; RotaryEncoder_Alps_EC11E-Switch_Vertical_H20mm_CircularMoun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

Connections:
+5V: A1.27 (+5V), J1.3, J5.1
+12V: A1.30 (VIN), J2.1, J2.3, J4.1, J6.1
/EC11A: A1.8 (D5), SW1.A
/EC11B: A1.7 (D4), SW1.B
/EC11SWA: A1.9 (D6), SW1.S1
/EC11SWB: A1.10 (D7), SW1.S2
/Heater: A1.6 (D3), R4.1
/Heater GND: J6.2, Q2.2 (D)
/SCL: A1.11 (D8), J1.2
/SDA: A1.12 (D9), J1.1
/Thermistor: A1.19 (A0), J5.2, R1.2
GND: A1.4 (GND), A1.29 (GND), J1.4, J2.2, J2.4, J4.2, Q2.3 (S), R1.1, R3.1, SW1.C
unnamed: Q2.1 (G), R3.2, R4.2

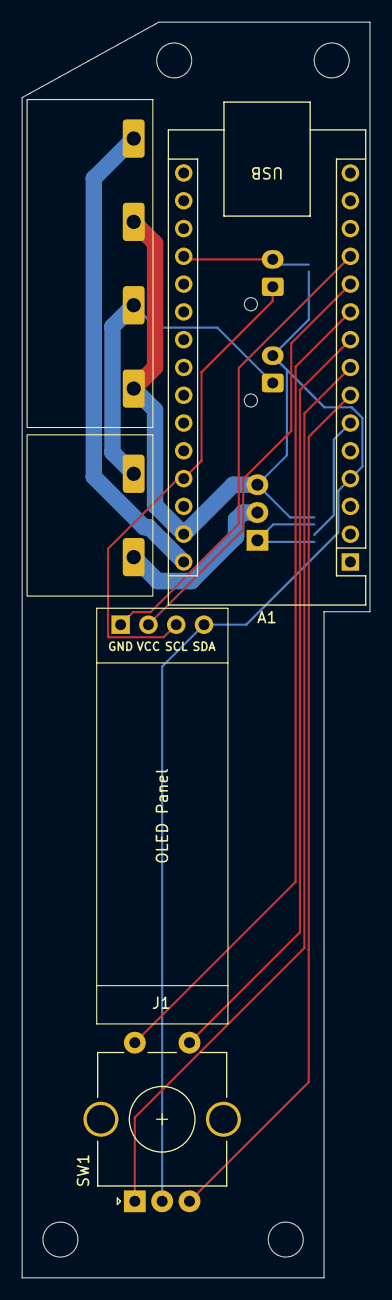
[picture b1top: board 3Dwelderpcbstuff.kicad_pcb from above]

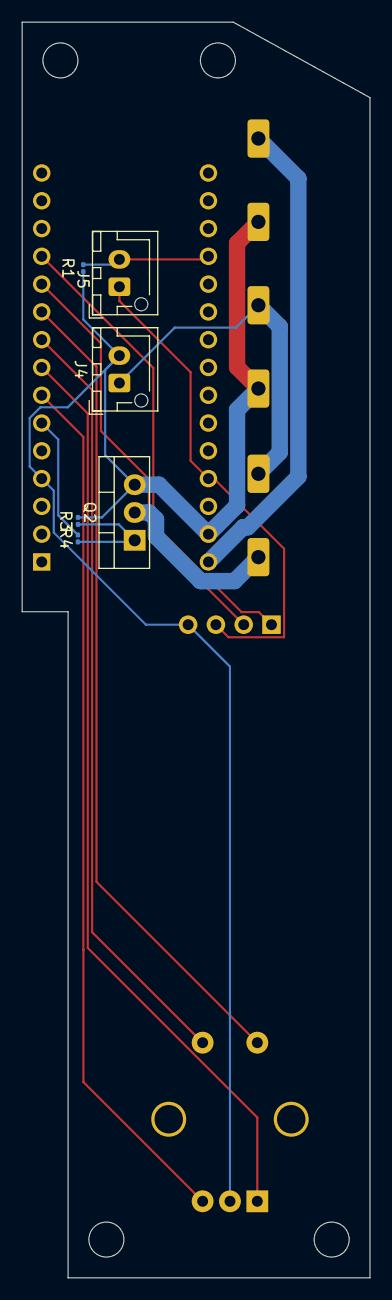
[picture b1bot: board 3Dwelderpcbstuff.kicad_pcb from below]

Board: 2 copper layers, 31.8 x 114.8 mm, 11 parts (6 on the bottom side), 13 nets.

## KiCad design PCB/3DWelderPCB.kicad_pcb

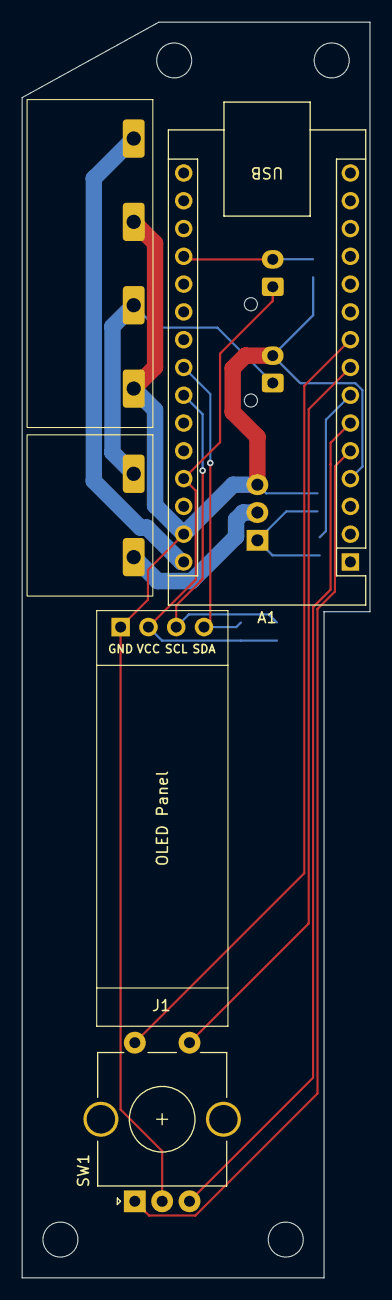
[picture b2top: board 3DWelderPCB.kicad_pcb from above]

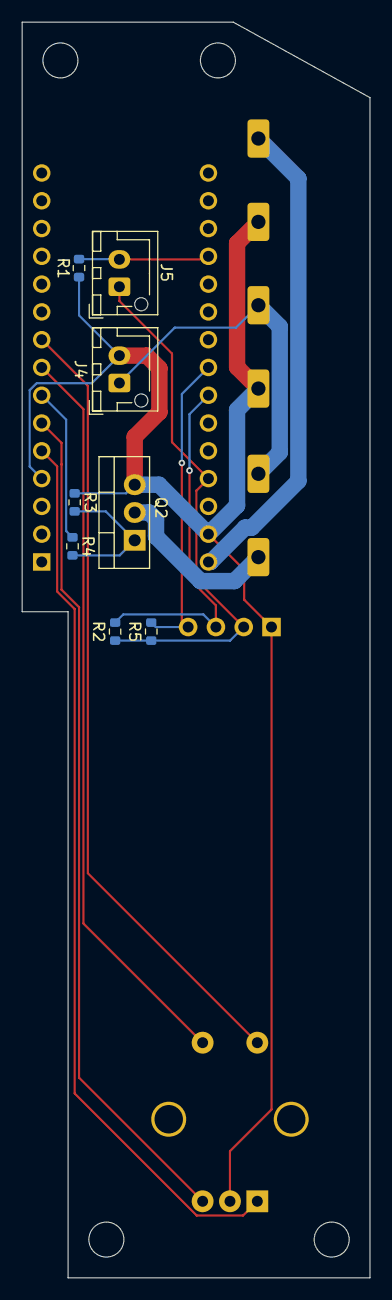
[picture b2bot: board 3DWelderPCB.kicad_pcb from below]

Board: 2 copper layers, 31.8 x 114.8 mm, 13 parts (8 on the bottom side), 14 nets.

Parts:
A1: Arduino_Nano_v3.x; Arduino_Nano
J1: 0.91in OLED Display; SSD1306-0.91-OLED-4pin-128x32
J2: Screw_Terminal_01x04 IN; Screw Terminal 4 Pin 7.62mmP
J4: 24V Fan; JST_XH_B2B-XH-AM_1x02_P2.50mm_Vertical
J5: Thermistor; JST_XH_B2B-XH-AM_1x02_P2.50mm_Vertical
J6: Screw_Terminal_01x02; Screw Terminal 2 Pin 7.62mmP
Q2: IRLZ34N; TO-220-3_Vertical
R1, R2, R5: 4.7K; R_0603_1608Metric
R3: R10k; R_0603_1608Metric
R4: R220; R_0603_1608Metric
SW1: EC11 RotaryEncoder_Switch; RotaryEncoder_Alps_EC11E-Switch_Vertical_H20mm_CircularMoun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

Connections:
+5V: A1.27 (+5V), J1.2, J5.1, R2.2, R5.2
+12V: A1.30 (VIN), J2.1
+24V: J2.3, J4.1, J6.1
EC11A: A1.5 (D2), SW1.A
EC11B: A1.6 (D3), SW1.B
EC11SWA: A1.8 (D5), SW1.S1
EC11SWB: A1.9 (D6), SW1.S2
GND: A1.4 (GND), A1.29 (GND), J1.1, J2.2, J2.4, J4.2, Q2.3 (S), R1.1, R3.1, SW1.C
Heater: A1.7 (D4), R4.1
Heater GND: J6.2, Q2.2 (D)
unnamed: Q2.1 (G), R3.2, R4.2
SCL: A1.24 (A5), J1.3, R2.1
SDA: A1.23 (A4), J1.4, R5.1
Thermistor: A1.19 (A0), J5.2, R1.2

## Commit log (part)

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2025-07-06 Create example
2025-07-27 Add step file
2025-08-08 Added new pcb, gerber, cad, pictures
2025-08-08 Updated CAD
2025-08-15 update code
2025-08-23 PCBV3
2025-11-12 changed layout
2026-03-26 adjusting comments
2026-03-29 lil capital
